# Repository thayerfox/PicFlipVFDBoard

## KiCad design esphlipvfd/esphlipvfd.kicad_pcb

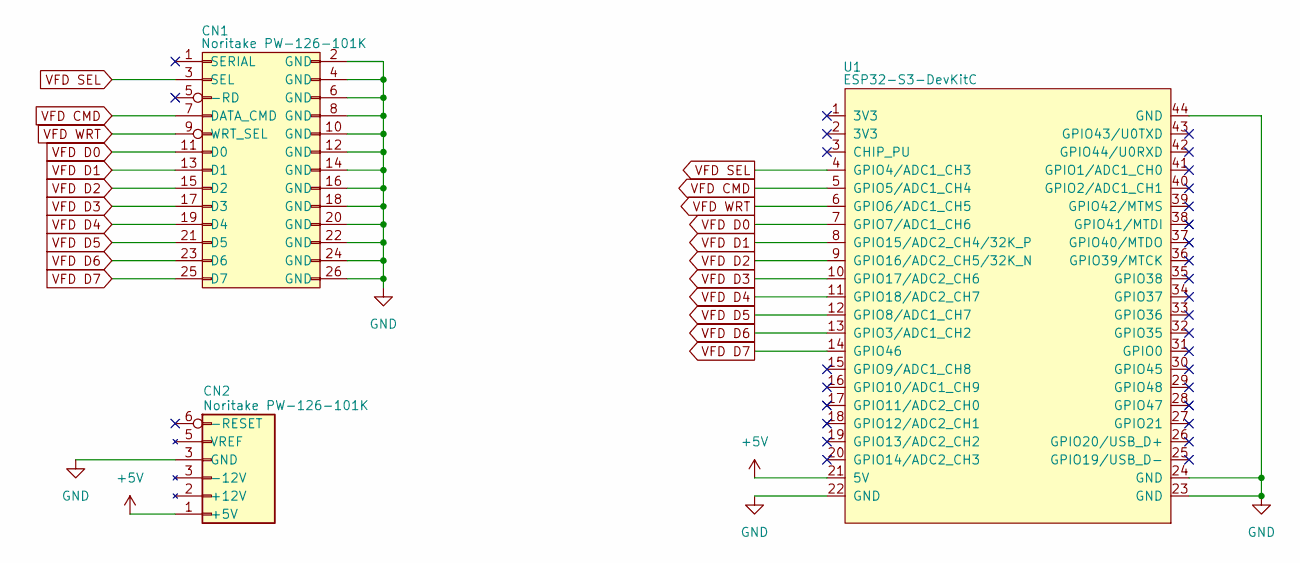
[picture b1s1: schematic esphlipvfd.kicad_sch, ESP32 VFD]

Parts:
CN1: Noritake PW-126-101K; IDC-Header_2x13_P2.54mm_Vertical
CN2: Noritake PW-126-101K; Molex_KK-396_5273-06A_1x06_P3.96mm_Vertical
U1: ESP32-S3-DevKitC

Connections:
+5V: CN2.1 (+5V), U1.21 (5V)
GND: CN1.2 (GND), CN1.4 (GND), CN1.6 (GND), CN1.8 (GND), CN1.10 (GND), CN1.12 (GND), CN1.14 (GND), CN1.16 (GND), CN1.18 (GND), CN1.20 (GND), CN1.22 (GND), CN1.24 (GND), CN1.26 (GND), CN2.3 (GND), U1.22 (GND), U1.23 (GND), U1.24 (GND), U1.44 (GND)
VFD CMD: CN1.7 (DATA_CMD), U1.5 (GPIO5/ADC1_CH4)
VFD D0: CN1.11 (D0), U1.7 (GPIO7/ADC1_CH6)
VFD D1: CN1.13 (D1), U1.8 (GPIO15/ADC2_CH4/32K_P)
VFD D2: CN1.15 (D2), U1.9 (GPIO16/ADC2_CH5/32K_N)
VFD D3: CN1.17 (D3), U1.10 (GPIO17/ADC2_CH6)
VFD D4: CN1.19 (D4), U1.11 (GPIO18/ADC2_CH7)
VFD D5: CN1.21 (D5), U1.12 (GPIO8/ADC1_CH7)
VFD D6: CN1.23 (D6), U1.13 (GPIO3/ADC1_CH2)
VFD D7: CN1.25 (D7), U1.14 (GPIO46)
VFD SEL: CN1.3 (SEL), U1.4 (GPIO4/ADC1_CH3)
VFD WRT: CN1.9 (WRT_SEL), U1.6 (GPIO6/ADC1_CH5)

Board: 2 copper layers, 3 parts (0 on the bottom side), 13 nets, no tracks yet.

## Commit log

2022-05-27 Initial from Paul
2022-05-27 weird extra projects????
2022-06-10 inital
2022-06-10 ignore backups folder
2022-07-18 Update for VFD datasheet
